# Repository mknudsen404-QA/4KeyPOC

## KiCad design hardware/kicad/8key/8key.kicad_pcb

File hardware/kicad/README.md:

# Switchboard keypad PCBs (KiCad 10)

Three real KiCad projects for the tiered USB agent-status keypad line described in
`docs/design/4key-product-line-idea.md`, and the V2 custom-PCB direction in
`SWITCHBOARD_DESIGN.md`.

| Project | Keys | Grid | Nickname on silkscreen | Board size |
| --- | --- | --- | --- | --- |
| `4key/` | 4 (3 agent slots + PTT) | 1 × 4 | THE STICK | 87.2 × 70.5 mm |
| `8key/` | 8 (7 agent slots + PTT) | 2 × 4 | THE SWITCH | 87.2 × 89.6 mm |
| `12key/` | 12 (11 agent slots + PTT) | 3 × 4 | THE CARROT | 87.2 × 108.7 mm |

The `4key` board is the drop-in electrical equivalent of the currently shipping
`firmware/neokey/neokey.ino` build: same 4 keys, same 3-agent + 1
push-to-talk split, same USB-serial JSON-lines protocol to
`host/switchboard_bridge.py`. It replaces the purchased Adafruit NeoKey 1x4
(and its Seesaw microcontroller) with one XL9555-class I2C expander and one
addressable-LED chain, per the V2 direction.

**Nothing here has been fabricated.** Read "Before you send these to a fab"
at the bottom — several dimensions in here are derived from community
references rather than manufacturer datasheets and must be verified.

## These files are generated

Do not hand-edit the `.kicad_sch` / `.kicad_pcb` files and expect the edit to
survive. One parametric definition drives all three tiers:

```
tools/boarddef.py   the single source of truth: parts, pin->net map,
                    placements, tier table, easter-egg data
tools/gen_sch.py    -> <tier>/<tier>.kicad_sch, .kicad_pro, sym-lib-table,
                       fp-lib-table   (system python3)
tools/gen_pcb.py    -> <tier>/<tier>.kicad_pcb   (KiCad's bundled python +
                       the pcbnew API, which is why it needs the interpreter
                       inside KiCad.app)
lib/switchboard.pretty/SW_Hotswap_Kailh_MX.kicad_mod
                    the one custom footprint (see caveats)
```

Regenerate everything:

```sh
cd hardware/kicad/tools
python3 gen_sch.py
/Applications/KiCad/KiCad.app/Contents/Frameworks/Python.framework/Versions/3.9/bin/python3.9 gen_pcb.py
```

Generating both sides from one table is deliberate: it is what guarantees the
schematic netlist and the board's pad nets cannot drift apart. If you start
editing the boards by hand in KiCad (which you will, to finish the routing),
stop regenerating and treat the files as the source from then on.

## Shared architecture (identical on all three tiers)

| Ref | Part | Role |
| --- | --- | --- |
| U1 | ESP32-S3-WROOM-1 (N16R8) | Controller. Native USB device, I2C master, LED data out. |
| U2 | XL9555 / PCF8575, TSSOP-24 | 16-bit I2C GPIO expander; reads every key. A2:A1:A0 = 000 → **0x20**. |
| U3 | AP2112K-3.3, SOT-23-5 | 5 V VBUS → 3V3 for U1 and U2. |
| U4 | 74LVC1G17, SOT-23-5 | Schmitt buffer powered from 5 V, so the LED chain sees a legal VIH instead of the ESP32's 3.3 V. |
| J1 | USB-C receptacle, 16P | Power + native USB serial. Sink only, 5.1 k CC pulldowns (R2/R3). |
| J2 | 2×6 pin header | Spare I2C + GPIO + rails, for a future encoder/display/second expander. |
| SW1..n | Gateron/MX-stem switch in a Kailh hot-swap socket | Keys. No switch is soldered to the board. |
| D1..n | SK6812MINI (PLCC4 3.5 × 3.5 mm) | One per-key RGB, top-mounted in the switch's SMD-LED window, daisy-chained. |
| CL1..n | 100 nF 0603 | One decoupling cap per LED. |

Firmware-visible pin map (matches `firmware/neokey/`'s `SDA_PIN 9` / `SCL_PIN 8`):

| ESP32-S3 pin | Net |
| --- | --- |
| IO9 | SDA |
| IO8 | SCL |
| IO5 | LED data (into U4, then a 330 Ω series resistor R7, then D1) |
| IO4 | expander `/INT` (so key scanning can be interrupt-driven instead of polled) |
| IO0 | BOOT button |
| EN | RESET button + RC |
| USB_D+ / USB_D− | J1 |

Key mapping rule for the whole line: **the bottom-right key is always
push-to-talk; every other key is an agent slot.** That keeps the firmware
generalisation trivial (`AGENT_KEY_COUNT = n-1`, `PTT_KEY_INDEX = n-1`) and
means the mic key doesn't move when a customer upgrades tiers. The trade-off
at the top tier is 11 agent slots, which is more parallel agents than most
people run; if you'd rather spend two of those keys on Approve/Cancel, that is
a `boarddef.py` edit plus a firmware change, not a board respin.

### What differs per tier

Only the key count, the row count (1/2/3 rows of 4), the board height, and the
easter-egg values. Same schematic, same parts, same expander: a single XL9555
has 16 I/O, so even the 12-key tier uses one chip with 4 spare I/O (brought
out as no-connects on the schematic). A second chained expander at 0x21 would
be needed only past 16 keys.

### Deliberate design notes

- **2-layer board, ground pour on both sides.** Signals run on F.Cu; the three
  nets that would otherwise have to cross everything (3V3 into the left-hand
  region, SDA, SCL) dive to B.Cu and cross underneath the pour, which flows
  around them. A handful of stitching vias tie the two pours together.
- **The ESP32-S3 PCB-antenna keepout is honoured**, as a notch in both ground
  pours plus the module footprint's own keepout. That is why the four mounting
  holes are not a symmetric rectangle — the top-left corner is inside the
  antenna keepout. This product does not use Wi-Fi/BLE, but the keepout is
  cheap to respect and leaves the option open.
- **Hot-swap only.** No switch solders to the board; MX-stem switches drop into
  Kailh sockets, matching the locked POC parts list.

## Easter-egg scheme: "The Tally" — lives on the enclosure

The version-identification scheme belongs to the **3D-printed case**, not the
board: see **`hardware/enclosure/`** for the badge geometry (parametric
`.scad` plus printable `.stl` per tier) and the full description of the
scheme. Short version — a Morse strip spelling the tier nickname, a revision
tally you can count by thumb, and a carrot-and-stick mascot that advances one
stage per tier.

The same marks are *also* on the back of each PCB, as a quieter second layer
only somebody who opens the case will ever see:

- **Morse strip** and **revision tally** on B.Silkscreen, bottom-left.
- **Graffiti tag** (`~ stick  r1  2026-09 ~`) instead of a sterile rev block.
- **The mascot** as a solder-mask *opening* over the back ground pour, so it
  comes out as bare plated copper on matte black. Being a mask aperture rather
  than a floating copper island, it costs nothing at the fab and can't cause a
  clearance problem.

Both sets are driven from `REV` / `BUILD_TAG` / `TIERS` in
`tools/boarddef.py`, so the case and the board can't disagree about which
revision they are — bump `REV`, regenerate both, done. If you'd rather the
board stayed plain and the case carried the whole joke, delete the
`easter_eggs()` call in `gen_pcb.py`'s `run()` and regenerate; nothing else
depends on it.

## ERC / DRC status — honestly

Checked with KiCad 10.0.6 (`kicad-cli`), all severities enabled. Re-verified
2026-10-03 after an independent pre-fab review (one Claude session, one Opus
session cross-checking it) found and fixed three real issues in the
generator — see "Fixed from that review" below.

| Board | ERC | DRC violations | DRC unconnected items |
| --- | --- | --- | --- |
| 4key | **0** | **0** | 39 |
| 8key | **0** | **0** | 43 |
| 12key | **0** | **0** | 47 |

(Unconnected-item counts went up from 34/38/42 because of the new ESD diode's
ratsnest — see below; nothing about the previously-routed nets changed.)

### Fixed from that review

1. **`gen_pcb.py` ignored `p.nc` entirely** (`gen_sch.py` already respected
   it). A pin listed in both `p.pins` (a plausible net name) and `p.nc`
   (explicitly unconnected — e.g. the last LED's DOUT, still called
   `LEDCH%d` even though nothing's next in the chain) got wired in the PCB
   but left as a no-connect in the schematic: real drift, the exact thing
   "one definition drives both generators" is supposed to prevent. Fixed by
   checking `p.nc` first in `place_parts()`, same as `gen_sch.py`'s
   `is_nc` check. Verified directly against the saved board with `pcbnew`
   (not just DRC, which couldn't see this): D4 pad 1 now reports no net,
   pads 2-4 unchanged.
2. **No bulk cap at U1's own +3V3 pin.** Added C9 (10 µF 0805) on the same
   net, T-tapped off the existing `(73.0,25.5)-(13.0,25.5)` B.Cu +3V3 trunk.
   Not literally at the pin — the entire left margin (U1's own body, C4,
   SW_BOOT, C7, U4, C6, SW_RST, R7 and their traces) is already packed
   solid; see the code comment on C9 in both `boarddef.py` and
   `gen_pcb.py`'s `route_strip()` for exactly where it landed instead and
   why every closer spot either crossed `LED_GPIO`'s run through that
   corner or sat on top of U1's own closely-pitched pin column.
3. **No USB ESD protection.** Added D_ESD, a USBLC6-2SC6 TVS array, shunted
   across the existing USB_DP/USB_DM/+5V/GND nets right near the connector
   (pinout confirmed against the actual symbol KiCad ships —
   `Power_Protection.kicad_sym`'s `USBLC6-2P6`, which `USBLC6-2SC6`
   extends: pins 1/6 = I/O1, pins 3/4 = I/O2, 2 = GND, 5 = VBUS). Left
   unrouted like the rest of the differential pair — this only adds the
   part and its net assignments to the schematic/BOM, not new copper.
4. A doc bug: `gen_pcb.py`'s own comment about the upper-left mounting
   hole's x-position said 49, the code uses 51.5.

Not changed from that review (deliberately, these are real judgment calls,
not generator bugs): a per-key decoupling cap (CL) that may clip the switch
housing (folds into the mandatory physical test-fit below, not something
DRC can see — the footprint's courtyard is deliberately clipped), and the
5V-side level-shifter's tighter-than-ideal voltage margin (works, documented
as a known tradeoff, a part swap is a bigger decision than this pass's
scope).

ERC is genuinely clean: every pin is either on a net or carries an explicit
no-connect, both rails have power flags, and the LDO output drives 3V3.

DRC reports **zero rule violations** — no clearance, crossing, shorting,
mask-bridge, courtyard, hole or silkscreen errors. The remaining
"unconnected items" are nets this generator deliberately did **not** route:

**Routed (by the generator):**

- GND — pours on F.Cu and B.Cu, thermal-relieved, with stitching vias.
- +5V — USB VBUS → bulk caps → LDO input/enable → level-shifter supply →
  right-margin trunk → a per-row bus feeding every LED's VDD and every
  per-key decoupling cap.
- +3V3 — LDO output → its bulk/decoupling caps → expander VCC → across the
  board on B.Cu → module 3V3 pin and its decoupling cap.
- SDA / SCL — module to expander, on B.Cu under the pour.
- The whole LED subsystem — IO5 → buffer → series resistor → `LEDCH0..n`
  daisy chain, including the row-to-row wraps on the 8- and 12-key boards.

**Left as ratsnest, for a human in the KiCad PCB editor:**

- `KEY1..KEYn` — every switch's signal pin to its expander I/O. Deliberate:
  this is the part where you actually want to choose the trace pattern by
  hand, and the assignment of key ↔ expander pin is still cheap to change.
  (Each switch's other pole already reaches the ground pour directly.)
- `USB_DP` / `USB_DM` — the USB 2.0 pair. Left for manual routing on purpose:
  a differential pair off a 0.5 mm-pitch connector wants a person's eye, not a
  script, and it is the one net where sloppy routing shows up as a device that
  intermittently fails to enumerate.
- `CC1` / `CC2` to R2/R3 — trivial, but in the same fine-pitch fan-out.
- `~RESET` and `BOOT` — button and RC nets in the left-hand region.
- `EXP_INT` and its pull-up R6.
- The I2C pull-ups R4/R5 and the EN pull-up R1 — placed, not wired.
- `J2` header nets (`HDR_*`).

So: power, ground, I2C and the entire LED chain are routed; the key matrix,
USB pair, and a handful of pull-ups/buttons are not. Expect an hour or two in
the PCB editor per tier to finish, and re-run DRC after.

Known non-blocking rule relaxations, set by `gen_pcb.py` and visible in the
board's design settings: minimum through-hole drill 0.15 mm (the
ESP32-S3-WROOM-1 footprint's own thermal vias are 0.2 mm), and minimum
resolved thermal spokes 1 instead of 2 (thermal relief is kept for
hand-soldering rather than switching the pour to solid connections).

## Symbols and footprints: what is real and what is a stand-in

All symbols and footprints are KiCad 10's bundled libraries except one custom
footprint. Status as of the 2026-10-03 pre-fab review (primary datasheets
fetched and checked pin-by-pin, not just read about):

- **U2's symbol is `Interface_Expansion:PCF8575DBR`, used as a stand-in for the
  XL9555 — now independently verified, not just assumed.** Checked against
  Xinluda's real XL9535/XL9555 datasheet (Rev 2.2, Table 2 Pin Functions,
  TSSOP24 column): pin 1=INT, 2=A1, 3=A2, 4-11=P00-07, 12=GND, 13-20=P10-17,
  21=A0, 22=SCL, 23=SDA, 24=VCC — an exact match to every pin `boarddef.py`
  assigns, including the two easiest things to get backwards (SCL/SDA not
  swapped; A0/A1/A2 all correctly grounded for address 0x20). The symbol,
  value field, and BOM still say PCF8575DBR, but the electrical assignment
  underneath it is confirmed correct.
- **`lib/switchboard.pretty/SW_Hotswap_Kailh_MX.kicad_mod` is hand-authored**
  from community references, not the Kailh datasheet. Its exact pad offsets
  (switch pins at ±5.08 mm/1.7 mm drill, hotswap barrels at (-3.81,-2.54) and
  (2.54,-5.08)/3.05 mm drill, 4 mm centre hole) match a pattern replicated
  across many open-source keyboard PCBs — corroborating, not conclusive.
  Physical test-fit (below) is still the one check that cannot be skipped.
- **The per-key LED's 5.0 mm south-of-centre offset is better justified than
  "an assumption"**: it matches the standard in-switch RGB convention (LED on
  the axis opposite the switch's own contact pins) to within 0.05 mm, and
  south-facing (the direction this design uses) is the orientation that
  avoids Cherry-profile keycap interference. Still worth confirming by eye
  during the test-fit, just not the open question it was.
- **The LED part/footprint pairing needs the exact SKU pinned down before
  ordering — this is the one real gap this review surfaced.**
  `boarddef.py` uses `LED_SMD:LED_SK6812MINI_PLCC4_3.5x3.5mm_P1.75mm` (the
  *plain* SK6812MINI, not the "-E" variant — KiCad ships both as genuinely
  different footprints, different size, different mount style). The plain
  part's own datasheet confirms its pinout matches this footprint and the
  code's comment (1=DOUT, 2=VSS, 3=DIN, 4=VDD), so the design itself isn't
  wrong — but its datasheet (checked directly) doesn't list a per-channel
  current figure the way the "-E" variant's does, so the current-budget
  numbers below should be re-confirmed against whichever exact SKU you
  actually order, not assumed to carry over from the "-E" part's spec.
- The ESP32-S3-WROOM-1 footprint — **now independently verified, all 41
  pins**, against Espressif's official datasheet v1.8 (Table 3-1), not just
  "should be fine": every pin `boarddef.py` assigns matches exactly,
  including the two it would have been easy to get backwards (pin 13=IO19=
  USB_D-, pin 14=IO20=USB_D+) and the two a bad search result once claimed
  were GPIOs instead of what they really are (pin 40=GND, pin 41=EPAD/GND,
  "connect directly to ground" per the datasheet itself). Confirm the module
  variant you buy is still N16R8 — the octal PSRAM on that variant consumes
  IO35/36/37, which is why those are no-connects here and must not be
  repurposed.
- USB-C, TSSOP-24, SOT-23-5/6, MountingHole, 0603/0805 and pin-header
  footprints are all stock KiCad and should be fine, but the USB-C receptacle
  footprint is for a specific part (`HCTL HC-TYPE-C-16P-01A`) — match what
  you actually buy.

## Before you send these to a fab

In rough order of how expensive it is to get wrong. Items marked **done**
were closed out in the 2026-10-03 review (one Claude session, one
independent Opus session cross-checking it); nothing here was taken on
faith from either — see the datasheet-level detail above and in
`docs/design/hardening-pass-plan.md`'s Workstream E.

1. **Print the key field 1:1 and test-fit a real Kailh hot-swap socket, a real
   Gateron MX switch, and a real SK6812MINI** (confirm the exact SKU first —
   see above). Confirm the socket pads, the 3.05 mm pin holes, the 4 mm
   centre hole, the ±5.08 mm plate holes, the LED window side, **and that a
   per-key decoupling cap (CL) doesn't clip the switch's own housing** — the
   footprint's courtyard is deliberately clipped there, so DRC can't catch
   this one. Still the one check that cannot be skipped.
2. **Done: ESP32-S3-WROOM-1 footprint verified** against Espressif's
   datasheet, all 41 pins. Still confirm the module variant you buy is
   N16R8.
3. **Done: 0x20 confirmed free** — this is a from-scratch board, nothing
   else shares the bus. A future >16-key chained expander needs A0 tied high
   for 0x21.
4. **Finish the unrouted nets** (`KEY1..KEYn`, `USB_DP`/`USB_DM`, `CC1`/`CC2`,
   `~RESET`/`BOOT`, `EXP_INT`, the I2C/EN pull-ups, `J2`, and now D_ESD's
   pads too — see "ERC / DRC status" above), then re-run DRC, then re-run
   `kicad-cli sch erc` after any schematic change.
5. **LED supply budget, with real numbers now**: SK6812MINI-E's datasheet
   (the closest verified reference — see the SKU caveat above) confirms
   12 mA per channel max, so ~36 mA/LED at full white + ~1 mA static. 4key's
   4 LEDs is ~150 mA worst case on the 5 V rail — comfortably inside what
   the design already budgets for (the 22 µF bulk cap and trace widths were
   already sized against the 12-key tier's ~700 mA worst case, which this is
   far under). Re-confirm once the exact SKU is locked.
6. **Done: USB ESD protection added** (D_ESD, USBLC6-2SC6) and **a second
   bulk cap added at U1's own +3V3 net** (C9) — see "Fixed from that review"
   above for exactly what and why.
7. **Check the USB-C shield-to-GND connection.** It is tied directly to GND
   here; some designs prefer a cap or ferrite. Fine either way, but decide it.
8. **Confirmed: there is no enclosure/case file in this repo to check the
   mounting-hole pattern against** (`hardware/enclosure/` holds only the
   per-tier version-badge tile — see its own README). This step is currently
   impossible to do, not just undone; revisit once a case model exists.
9. **Trademark-check the tier nicknames before they go on a product — treat
   all three as internal codenames until then.** "THE SWITCH" is the one to
   worry about: it's on the silkscreen, sits in the same product class
   (electronic devices) as Nintendo's Switch trademark, and Nintendo
   enforces that mark aggressively. "THE STICK" and "THE CARROT" brush
   weaker but real neighbors (Fire TV Stick/Memory Stick; the CARROT app
   family) in the same class. All three are bare dictionary words, so even
   a clear mark would be weak — but that cuts both ways; it's not a defense
   against getting a cease-and-desist first. This needs a real TESS search
   or an attorney, not the casual web search this review used as a gut-check
   — see the IP section of `docs/design/4key-business-plan.md`. Nothing here
   uses "Claude" or "Codex". Also worth a line item next to it: the
   hot-swap footprint's community-reference provenance — some
   keyboard-community footprint libraries are share-alike licensed, which
   could attach to these PCB files; not checked this pass.
10. Order a black-soldermask / white-silkscreen board (already set in the
    stackup) and ENIG if you want the bare-copper mascot to look good and not
    oxidise. Decide fab house and batch quantity (most fabs have a 5-board
    minimum even for "one") before submitting.

## r2 fix — hot-swap socket pads moved to B.Cu (2026-10-14)

The r1 boards (stick r1, 2026-09) came back with the Kailh socket pads on
**F.Cu**, the same side the switch plugs into, and the switch pin holes are
non-plated — so no key could connect. Fixed:

- `lib/switchboard.pretty/SW_Hotswap_Kailh_MX.kicad_mod`: pads 1/2 now on
  `B.Cu`/`B.Paste`/`B.Mask` (same positions — standard Kailh MX geometry).
- All three `.kicad_pcb` files patched in place (not regenerated, so the
  hand/FreeRouting work is kept): socket pads moved to B.Cu, a via added at
  the centre of each routed pad 1 to reach the existing F.Cu KEY trace, and
  all zone fills stripped — **refill zones (B) before DRC/plotting**.
- 12key: KEY5, KEY6, KEY9, KEY10, KEY11 ran on B.Cu straight through the new
  pad sites, so they were ripped up and re-routed with FreeRouting (existing
  wiring locked as `protect`, GND in an ignored class since the pours carry
  it; sub-0.15 mm neck-downs widened to the 0.15 mm board minimum). Same
  GND-island and LEDCH0 fixes as 4key below, plus a via under J1 A1/B12,
  whose pads were boxed in by the USB_DP route. DRC clean, 0 unconnected.
  Outline is 87.3 × 135.75 mm (bigger than the old 120.65 mm quote).
- 8key: KEY nets were never routed; still need routing.
- `tools/gen_pcb.py` route_strip(): adds the same pad-centre via.
- r1 originals are in git history: `git show 81d7b05:hardware/kicad/4key/4key.kicad_pcb` (same commit for 8key; 12key r1 is `58fec66~1`).

### 4key r2 cleanup (2026-10-14) — DRC clean, 0 unconnected

Running DRC on r1 (its stored fills = what was fabricated) turned up real
faults on top of the socket problem. Physical copper connectivity on r1:

- **GND split into 8 pieces.** Only the pour around the ESP32/LEDs/keys
  reaches the USB-C ground. Isolated: U3 (AP2112 LDO) GND with C1/C2/C3,
  all four U2 (expander) GND pins with C5/C9, R2 and R3 (the 5.1k CC
  pull-downs) with C8, and D_ESD. So the LDO has no ground return (no clean
  3V3), the expander has no reliable ground, and C-to-C chargers won't supply VBUS.
  r1 boards are not usable. Fixed with 9 stitching vias (R3 gets its own via
  at (163.9, 110.75) plus a short trace).
- **+3V3 opens**: R4/R5/R6 (SDA, SCL, EXP_INT pull-ups) were an island, and
  J2 pin 1 stopped 3 mm short of its pad. J2 now reached via a FreeRouting
  detour round the USB_DP via; R4 chain fed from U2 pin 24 through a via at
  (165.3, 137.4) and a short B.Cu run. (The x=173 trunk was also split at
  its T-junctions so KiCad sees them as connected; those were fine in
  copper.)
- **LEDCH0 0.075 mm from SW_RST GND pad**: trace moved to x=103.8, ~RESET
  via nudged to (104.6, 145.183) to make room.
- USB_DP exit from J1 A6 straightened (was 0.192 mm from A7).

Remaining warnings are cosmetic: 6 silk-clipped-by-mask on the socket
outlines, and schematic-parity noise (board net names lack the `/` prefix,
footprint IDs lack the library nickname, mounting holes H38–H41 are
board-only).

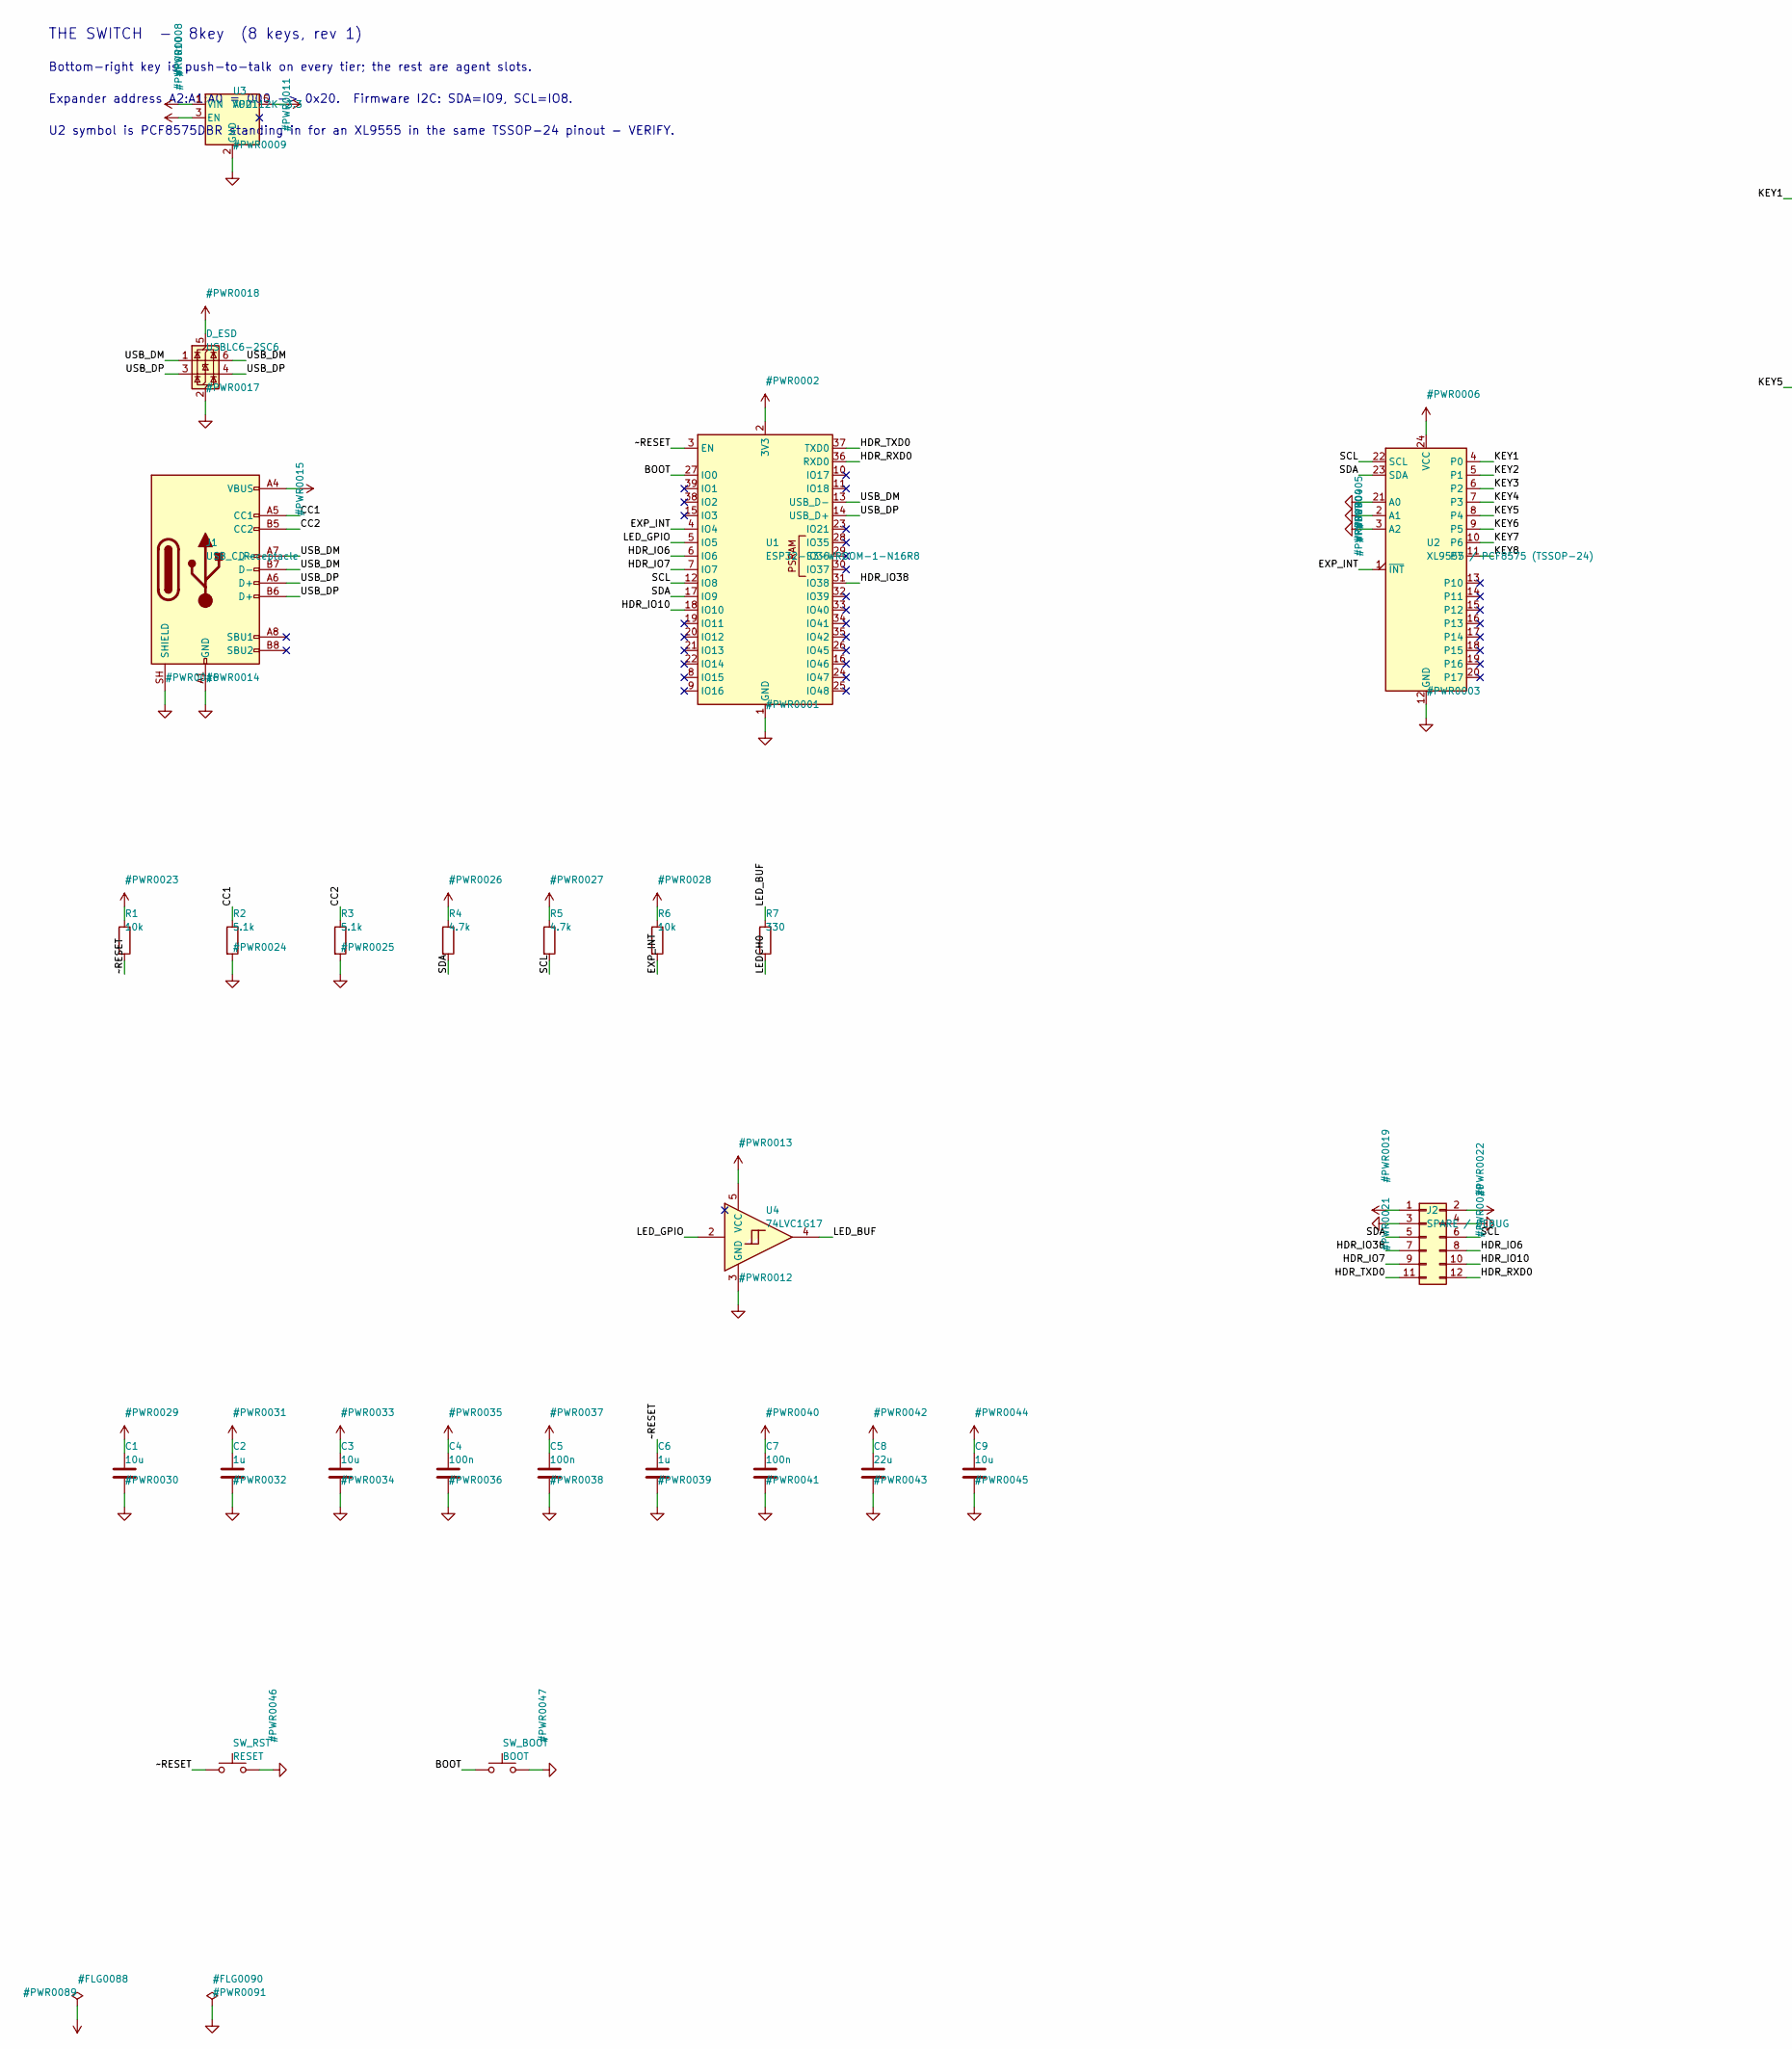
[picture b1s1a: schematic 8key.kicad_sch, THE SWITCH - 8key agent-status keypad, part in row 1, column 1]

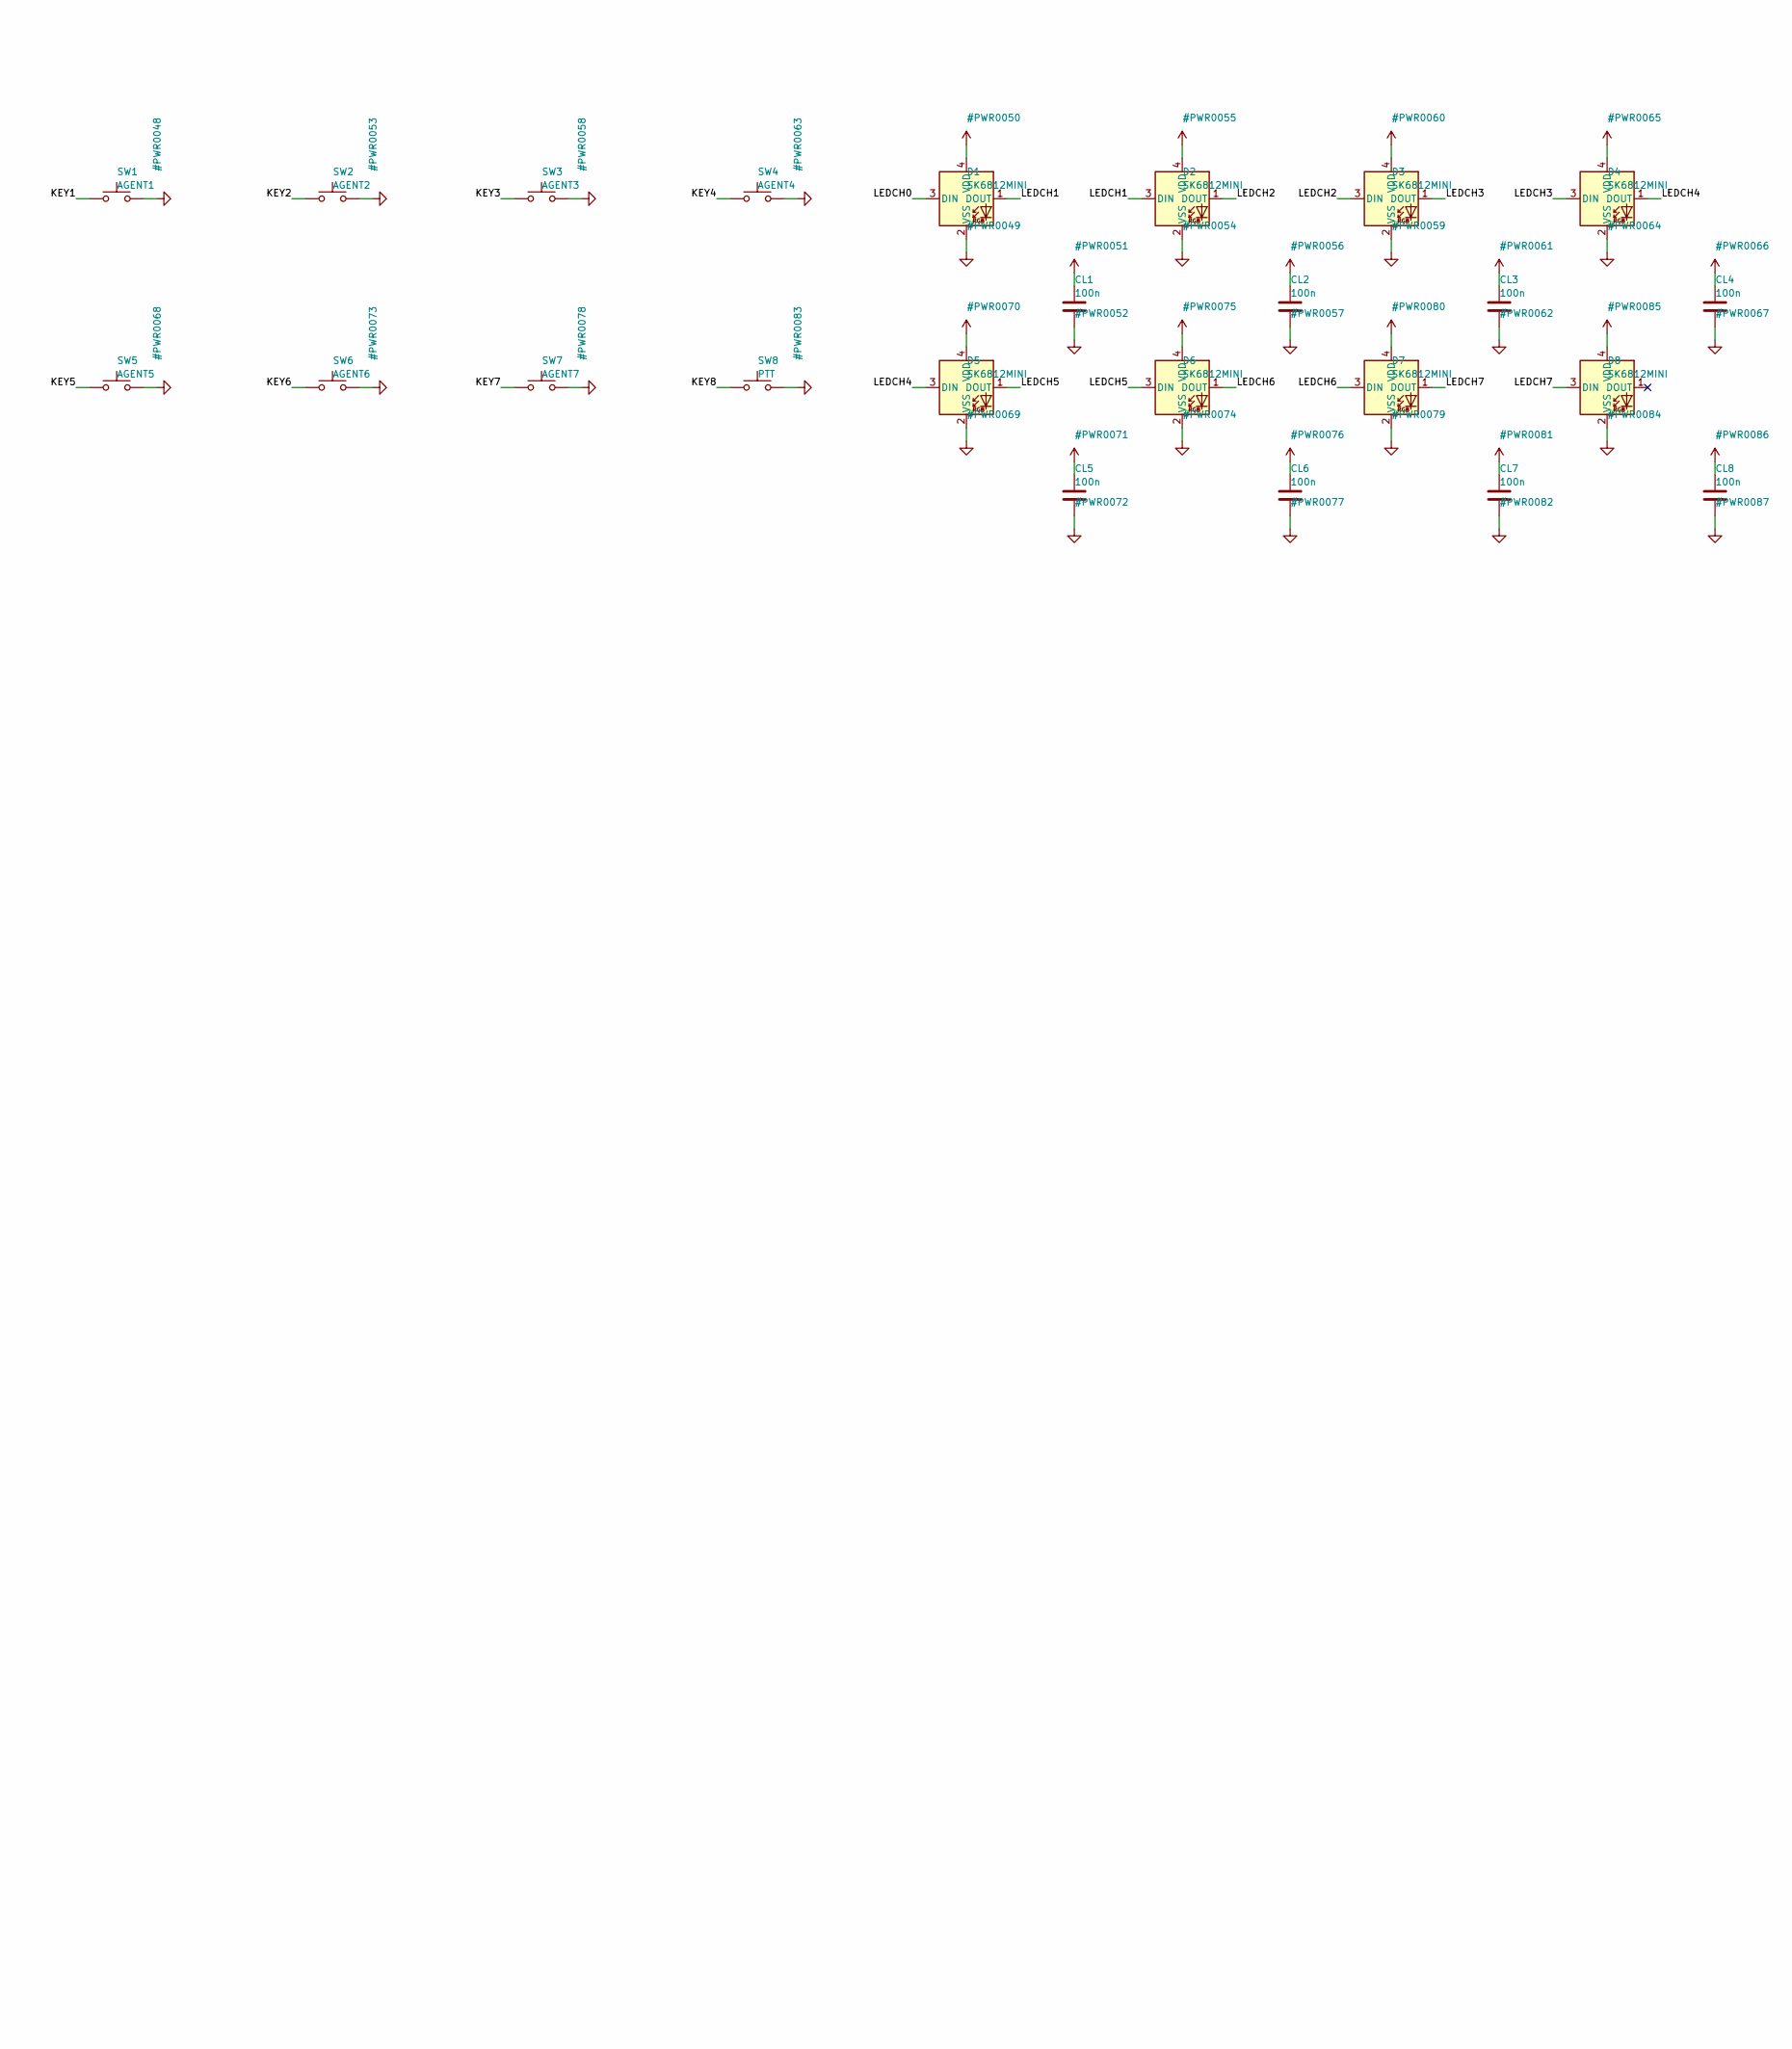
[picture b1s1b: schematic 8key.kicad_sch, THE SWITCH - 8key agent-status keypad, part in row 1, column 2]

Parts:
C1, C3, C9: 10u; C_0805_2012Metric_Pad1.18x1.45mm_HandSolder
C2, C6: 1u; C_0603_1608Metric_Pad1.08x0.95mm_HandSolder
C4, C5, C7: 100n; C_0603_1608Metric_Pad1.08x0.95mm_HandSolder
C8: 22u; C_0805_2012Metric_Pad1.18x1.45mm_HandSolder
CL1, CL2, CL3, CL4, CL5, CL6, CL7, CL8: 100n; C_0603_1608Metric_Pad1.08x0.95mm_HandSolder
D1, D2, D3, D4, D5, D6, D7, D8: SK6812MINI; LED_SK6812MINI_PLCC4_3.5x3.5mm_P1.75mm
D_ESD: USBLC6-2SC6; SOT-23-6
J1: USB_C_Receptacle; USB_C_Receptacle_HCTL_HC-TYPE-C-16P-01A
J2: SPARE / DEBUG; PinHeader_2x06_P2.54mm_Vertical
R1, R6: 10k; R_0603_1608Metric_Pad0.98x0.95mm_HandSolder
R2, R3: 5.1k; R_0603_1608Metric_Pad0.98x0.95mm_HandSolder
R4, R5: 4.7k; R_0603_1608Metric_Pad0.98x0.95mm_HandSolder
R7: 330; R_0603_1608Metric_Pad0.98x0.95mm_HandSolder
SW1: AGENT1; SW_Hotswap_Kailh_MX
SW2: AGENT2; SW_Hotswap_Kailh_MX
SW3: AGENT3; SW_Hotswap_Kailh_MX
SW4: AGENT4; SW_Hotswap_Kailh_MX
SW5: AGENT5; SW_Hotswap_Kailh_MX
SW6: AGENT6; SW_Hotswap_Kailh_MX
SW7: AGENT7; SW_Hotswap_Kailh_MX
SW8: PTT; SW_Hotswap_Kailh_MX
SW_BOOT: BOOT; SW_Push_1P1T_NO_CK_KMR2
SW_RST: RESET; SW_Push_1P1T_NO_CK_KMR2
U1: ESP32-S3-WROOM-1-N16R8; ESP32-S3-WROOM-1
U2: XL9555 / PCF8575 (TSSOP-24); TSSOP-24_4.4x7.8mm_P0.65mm
U3: AP2112K-3.3; SOT-23-5
U4: 74LVC1G17; SOT-23-5

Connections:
+3V3: C3.1, C4.1, C5.1, C9.1, J2.1, R1.1, R4.1, R5.1, R6.1, U1.2 (3V3), U2.24 (VCC), U3.5 (VOUT)
+5V: C1.1, C2.1, C7.1, C8.1, CL1.1, CL2.1, CL3.1, CL4.1, CL5.1, CL6.1, CL7.1, CL8.1, D1.4 (VDD), D2.4 (VDD), D3.4 (VDD), D4.4 (VDD), D5.4 (VDD), D6.4 (VDD), D7.4 (VDD), D8.4 (VDD), D_ESD.5 (VBUS), J1.A4 (VBUS), J1.A9 (VBUS), J1.B4 (VBUS), J1.B9 (VBUS), J2.2, U3.1 (VIN), U3.3 (EN), U4.5 (VCC)
BOOT: SW_BOOT.1, U1.27 (IO0)
CC1: J1.A5 (CC1), R2.1
CC2: J1.B5 (CC2), R3.1
EXP_INT: R6.2, U1.4 (IO4), U2.1 (~INT)
GND: C1.2, C2.2, C3.2, C4.2, C5.2, C6.2, C7.2, C8.2, C9.2, CL1.2, CL2.2, CL3.2, CL4.2, CL5.2, CL6.2, CL7.2, CL8.2, D1.2 (VSS), D2.2 (VSS), D3.2 (VSS), D4.2 (VSS), D5.2 (VSS), D6.2 (VSS), D7.2 (VSS), D8.2 (VSS), D_ESD.2 (GND), J1.A1 (GND), J1.A12 (GND), J1.B1 (GND), J1.B12 (GND), J1.SH (SHIELD), J2.3, J2.4, R2.2, R3.2, SW1.2, SW2.2, SW3.2, SW4.2, SW5.2, SW6.2, SW7.2, SW8.2, SW_BOOT.2, SW_RST.2, U1.1 (GND), U1.40 (GND), U1.41 (GND), U2.2 (A1), U2.3 (A2), U2.12 (GND), U2.21 (A0), U3.2 (GND), U4.3 (GND)
HDR_IO6: J2.8, U1.6 (IO6)
HDR_IO7: J2.9, U1.7 (IO7)
HDR_IO10: J2.10, U1.18 (IO10)
HDR_IO38: J2.7, U1.31 (IO38)
HDR_RXD0: J2.12, U1.36 (RXD0)
HDR_TXD0: J2.11, U1.37 (TXD0)
KEY1: SW1.1, U2.4 (P0)
KEY2: SW2.1, U2.5 (P1)
KEY3: SW3.1, U2.6 (P2)
KEY4: SW4.1, U2.7 (P3)
KEY5: SW5.1, U2.8 (P4)
KEY6: SW6.1, U2.9 (P5)
KEY7: SW7.1, U2.10 (P6)
KEY8: SW8.1, U2.11 (P7)
LEDCH0: D1.3 (DIN), R7.2
LEDCH1: D1.1 (DOUT), D2.3 (DIN)
LEDCH2: D2.1 (DOUT), D3.3 (DIN)
LEDCH3: D3.1 (DOUT), D4.3 (DIN)
LEDCH4: D4.1 (DOUT), D5.3 (DIN)
LEDCH5: D5.1 (DOUT), D6.3 (DIN)
LEDCH6: D6.1 (DOUT), D7.3 (DIN)
LEDCH7: D7.1 (DOUT), D8.3 (DIN)
LED_BUF: R7.1, U4.4
LED_GPIO: U1.5 (IO5), U4.2
SCL: J2.6, R5.2, U1.12 (IO8), U2.22 (SCL)
SDA: J2.5, R4.2, U1.17 (IO9), U2.23 (SDA)
USB_DM: D_ESD.1 (I/O1), D_ESD.6 (I/O1), J1.A7 (D-), J1.B7 (D-), U1.13 (USB_D-)
USB_DP: D_ESD.3 (I/O2), D_ESD.4 (I/O2), J1.A6 (D+), J1.B6 (D+), U1.14 (USB_D+)
~RESET: C6.1, R1.2, SW_RST.1, U1.3 (EN)

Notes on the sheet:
THE SWITCH - 8key (8 keys, rev 1)
Bottom-right key is push-to-talk on every tier; the rest are agent slots.
Expander address A2:A1:A0 = 000 -> 0x20. Firmware I2C: SDA=IO9, SCL=IO8.
U2 symbol is PCF8575DBR standing in for an XL9555 in the same TSSOP-24 pinout - VERIFY.

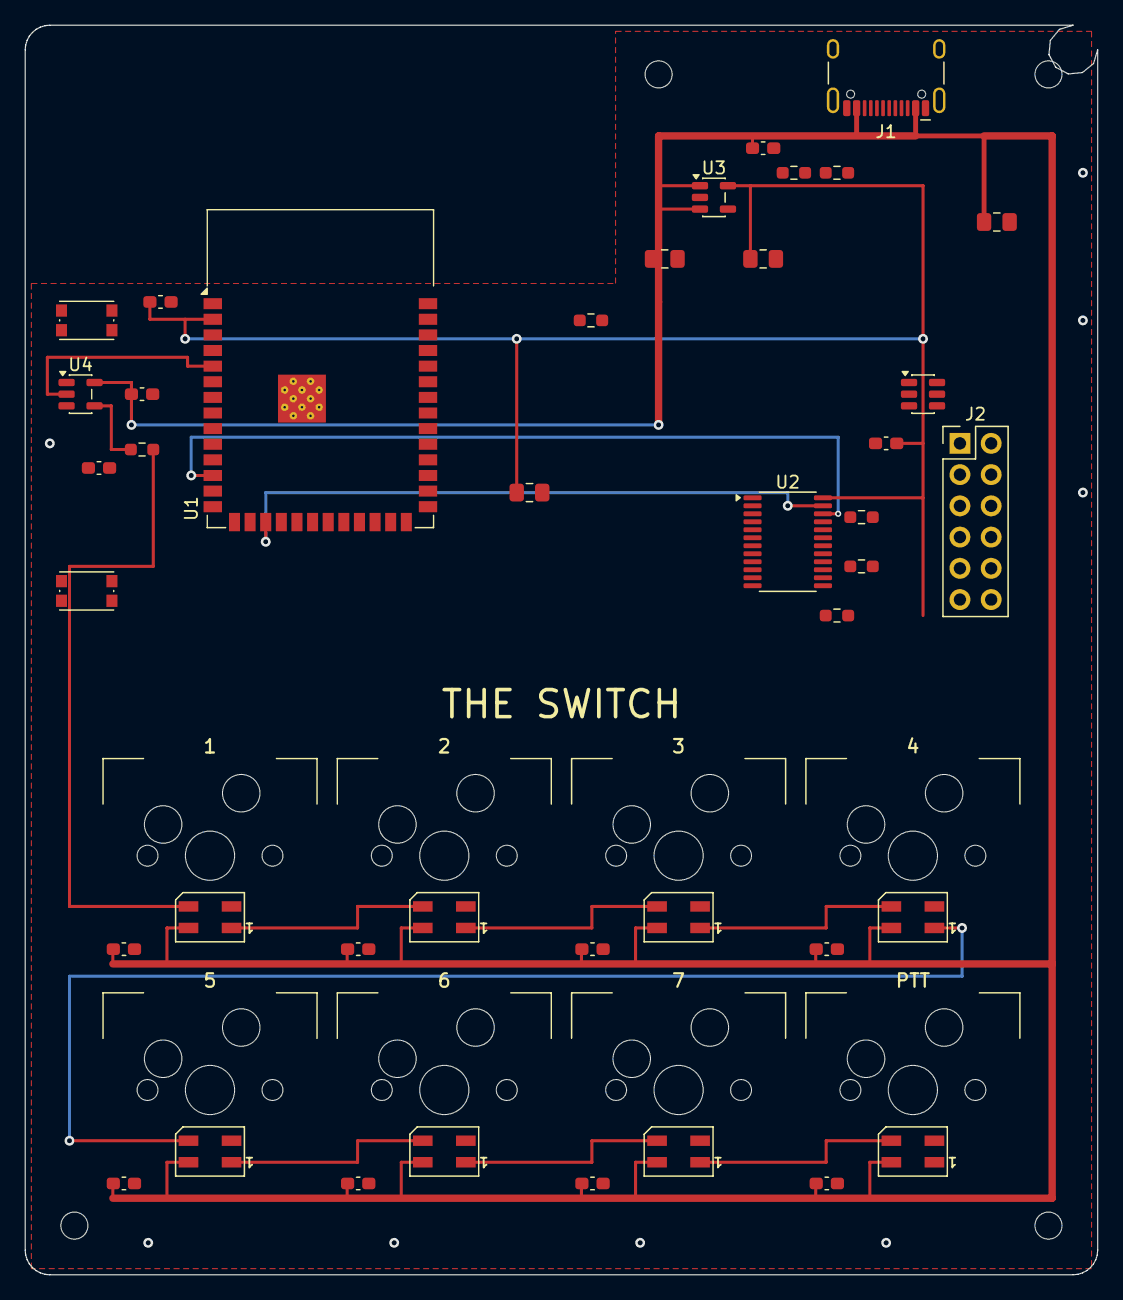
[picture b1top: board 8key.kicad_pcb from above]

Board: 2 copper layers, 87.2 x 101.6 mm, 53 parts (0 on the bottom side), 36 nets.

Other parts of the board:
H50, H51, H52, H53: MountingHole_2.2mm_M2
